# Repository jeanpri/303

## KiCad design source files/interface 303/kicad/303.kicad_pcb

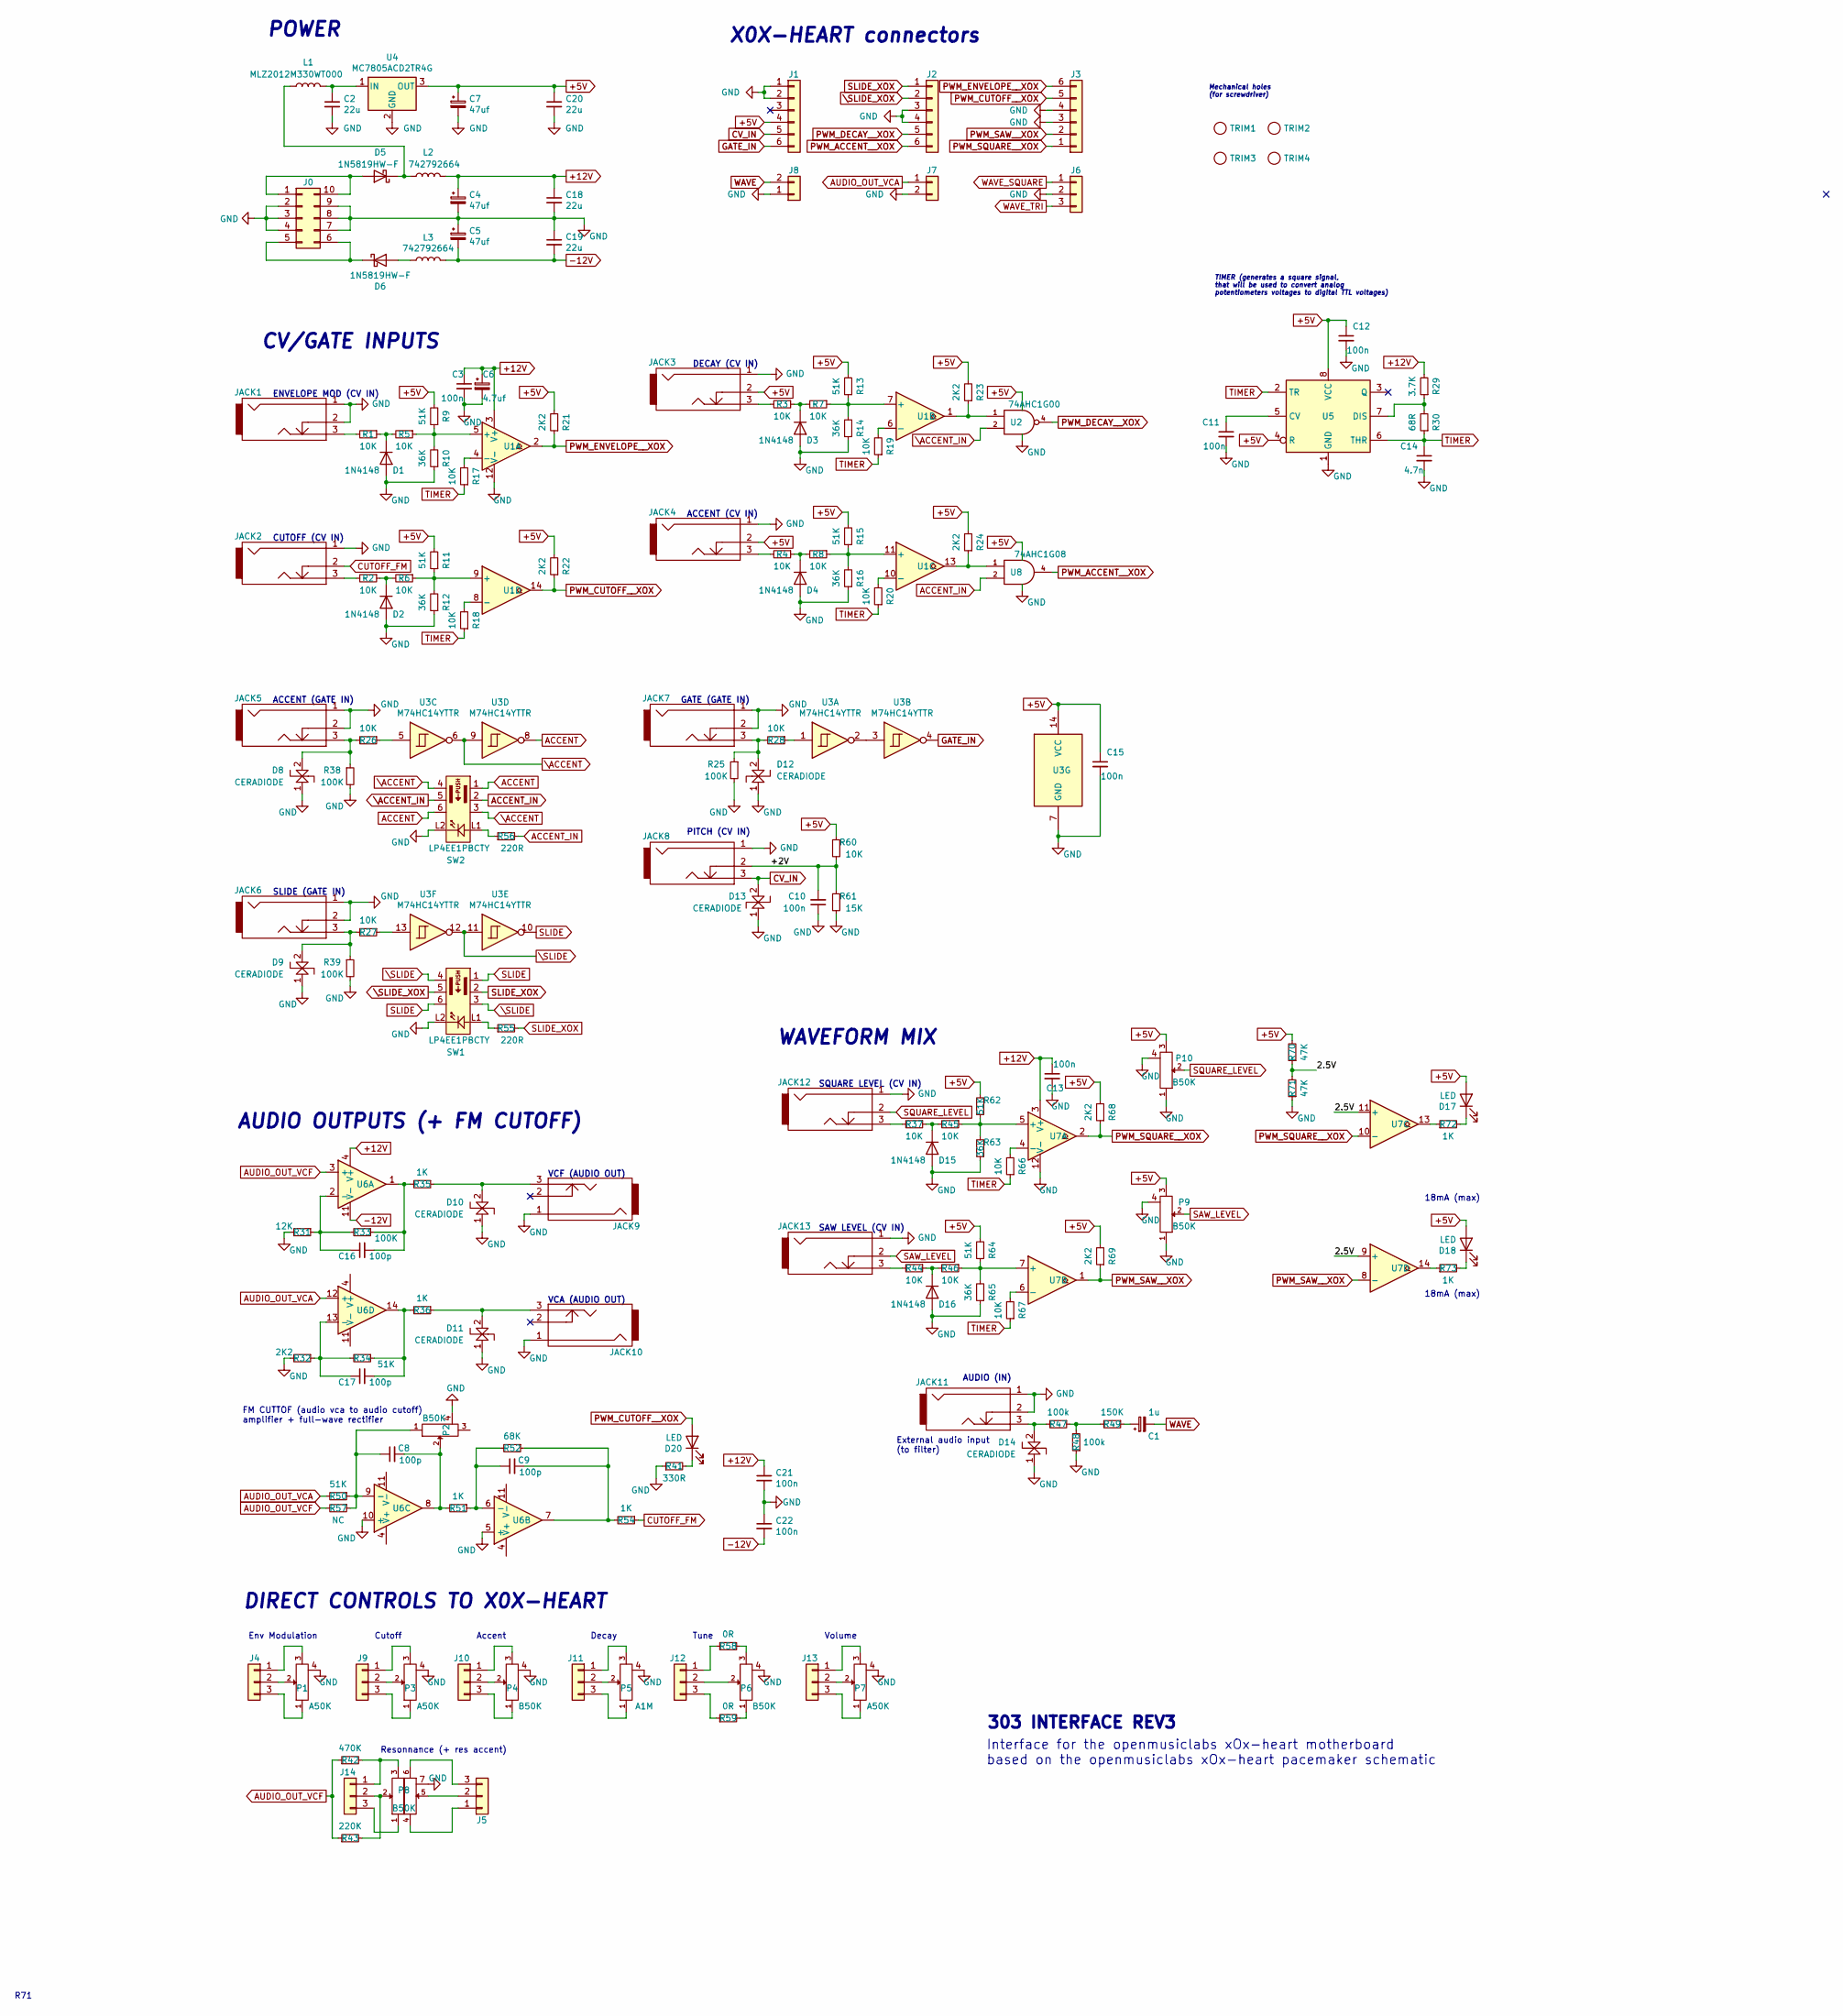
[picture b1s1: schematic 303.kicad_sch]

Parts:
C1: 1u; CP_4x5.3
C2, C18, C19, C20: 22u; C_1206
C3, C10, C11, C12, C13, C15, C21, C22: 100n; C_0603
C4, C5, C7: 47uf; CP_6.3x5.8
C6: 4.7uf; CP_5x5.8
C8, C9, C16, C17: 100p; C_0603
C14: 4.7n; C_0603
D1, D2, D3, D4, D15, D16: 1N4148; D_SOD-123
D5, D6: 1N5819HW-F; D_SOD-123
D8, D9, D10, D11, D12, D13, D14: CERADIODE; CERA_0603
D17, D18, D20: LED; LED_D3.0mm
J0: 30310-6002HB
J1, J2, J3: Conn_01x06; PinHeader_1x06_P2.54mm_Vertical
J4, J5, J6, J9, J10, J11, J12, J13, J14: Conn_01x03; PinHeader_1x03_P2.54mm_Vertical
J7, J8: Conn_01x02; PinHeader_1x02_P2.54mm_Vertical
JACK1, JACK2, JACK3, JACK4, JACK12, JACK13: PJ398SM-BLACK; Thonkiconn_small_head_to_head
JACK5, JACK6, JACK7, JACK8, JACK9, JACK10, JACK11: PJ398SM-BLACK; Thonkiconn_small
L1: MLZ2012M330WT000; R_0805
L2, L3: 742792664; R_0603
P1, P3, P7: A50K; Alpha9mm
P2, P4, P6, P9, P10: B50K; Alpha9mm
P5: A1M; Alpha9mm
P8: B50K; Alpha9mm_dual
R1, R2, R3, R4, R5, R6, R7, R8, R17, R18, R19, R20, R26, R27, R28, R37, R44, R45, R46, R60, R66, R67: 10K; R_0805
R9, R11, R13, R15, R34, R50, R62, R64: 51K; R_0805
R10, R12, R14, R16, R63, R65: 36K; R_0805
R21, R22, R23, R24, R32, R68, R69: 2K2; R_0805
R25, R33, R38, R39: 100K; R_0805
R29: 3.7K; R_0805
R30: 68R; R_0805
R31: 12K; R_0805
R35, R36, R51, R54, R72, R73: 1K; R_0805
R41: 330R; R_0805
R42: 470K; R_0805
R43: 220K; R_0805
R47, R48: 100k; R_0805
R49: 150K; R_0805
R52: 68K; R_0805
R55, R56: 220R; R_0805
R57: NC; R_0805
R58, R59: 0R; R_0805
R61: 15K; R_0805
R70, R71: 47K; R_0805
SW1, SW2: LP4EE1PBCTY; LP4EE1PBCT
TRIM1, TRIM2, TRIM3, TRIM4: TRIM; HOLE_5_2mm
U1, U7: LM339AMX/NOPB; SOIC-14_3.9x8.7mm_P1.27mm
U2: 74AHC1G00; SOT-23-5
U3: M74HC14YTTR; TSSOP-14_4.4x5mm_P0.65mm
U4: MC7805ACD2TR4G; TO-263-3_TabPin2
U5: LM555CMMX/NOPB; VSSOP-8_3.0x3.0mm_P0.65mm
U6: TL074IDE4; SOIC-14_3.9x8.7mm_P1.27mm
U8: 74AHC1G08; SOT-23-5

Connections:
+5V: C7.1, C12.1, C15.1, C20.1, D17.2 (A), D18.2 (A), J1.4, JACK3.2, JACK4.2, P9.3, P10.3, R9.2, R11.2, R13.2, R15.2, R21.2, R22.2, R23.2, R24.2, R60.1, R62.2, R64.2, R68.2, R69.2, R70.2, U2.5 (VCC), U3.14 (VCC), U4.3 (OUT), U5.4 (R), U5.8 (VCC), U8.5 (VCC)
+12V: C3.1, C4.1, C6.1, C13.1, C18.1, C21.1, L2.2, R29.2, U1.3 (V+), U6.4 (V+), U7.3 (V+)
-12V: C5.2, C19.2, C22.2, L3.2, U6.11 (V-)
/2.5V: R70.1, R71.2, U7.9 (+), U7.11 (+)
/+2V: C10.2, JACK8.2, R60.2, R61.1
ACCENT: SW2.1, SW2.6, U3.8
ACCENT_IN: R56.2, SW2.2, U8.2
AUDIO_OUT_VCA: J7.1, R50.2, U6.12 (+)
AUDIO_OUT_VCF: R42.1, R43.1, R57.2, U6.3 (+)
CUTOFF_FM: JACK2.2, R54.1
CV_IN: D13.2, J1.5, JACK8.3
GATE_IN: J1.6, U3.4
GND: C2.2, C3.2, C4.2, C5.1, C6.2, C7.2, C10.1, C11.2, C12.2, C13.2, C14.2, C15.2, C18.2, C19.1, C20.2, C21.2, C22.1, D1.2 (A), D2.2 (A), D3.2 (A), D4.2 (A), D8.1, D9.1, D10.1, D11.1, D12.1, D13.1, D14.1, D15.2 (A), D16.2 (A), J0.2, J0.3, J0.4, J0.7, J0.8, J0.9, J1.1, J1.2, J2.3, J2.4, J3.3, J3.4, J6.2, J7.2, J8.1, JACK1.1, JACK1.2, JACK2.1, JACK3.1, JACK4.1, JACK5.1, JACK5.2, JACK6.1, JACK6.2, JACK7.1, JACK7.2, JACK8.1, JACK9.1, JACK10.1, JACK11.1, JACK11.2, JACK12.1, JACK13.1, P1.4 (shield), P2.4 (shield), P3.4 (shield), P4.4 (shield), P5.4 (shield), P6.4 (shield), P7.4 (shield), P8.7 (shield), P9.1, P9.4 (shield), P10.1, P10.4 (shield), R10.1, R12.1, R14.1, R16.1, R25.2, R31.2, R32.2, R38.2, R39.2, R41.1, R48.1, R61.2, R63.1, R65.1, R71.1, SW1.L2, SW2.L2, U1.12 (V-), U2.3 (GND), U3.7 (GND), U4.2 (GND), U5.1 (GND), U6.5 (+), U6.10 (+), U7.12 (V-), U8.3 (GND)
unnamed: C1.1, R49.1
unnamed: C8.2, P2.2, R51.2, U6.8
unnamed: C9.2, R52.1, R54.2, U6.7
unnamed: C16.2, R33.1, R35.2, U6.1
unnamed: C17.2, R34.1, R36.2, U6.14
unnamed: D1.1 (K), R1.1, R5.2
unnamed: D2.1 (K), R2.1, R6.2
unnamed: D3.1 (K), R3.1, R7.2
unnamed: D4.1 (K), R4.1, R8.2
unnamed: D5.2 (A), J0.1, J0.10
unnamed: D5.1 (K), L1.1, L2.1
unnamed: D6.2 (A), L3.1
unnamed: D6.1 (K), J0.5, J0.6
unnamed: D8.2, JACK5.3, R26.2, R38.1
unnamed: D9.2, JACK6.3, R27.2, R39.1
unnamed: D10.2, JACK9.3, R35.1
unnamed: D11.2, JACK10.3, R36.1
unnamed: D12.2, JACK7.3, R25.1, R28.2
unnamed: D14.2, JACK11.3, R47.2
unnamed: D15.1 (K), R37.1, R45.2
unnamed: D16.1 (K), R44.1, R46.2
unnamed: D17.1 (K), R72.2
unnamed: D18.1 (K), R73.2
unnamed: D20.1 (K), R41.2
unnamed: J4.1, P1.3
unnamed: J4.2, P1.2
unnamed: J4.3, P1.1
unnamed: J5.1, P8.4
unnamed: J5.2, P8.5
unnamed: J5.3, P8.6
unnamed: J9.1, P3.3
unnamed: J9.2, P3.2
unnamed: J9.3, P3.1
unnamed: J10.1, P4.3
unnamed: J10.2, P4.2
unnamed: J10.3, P4.1
unnamed: J11.1, P5.3
unnamed: J11.2, P5.2
unnamed: J11.3, P5.1
unnamed: J12.1, R58.1
unnamed: J12.2, P6.2
unnamed: J12.3, R59.1
unnamed: J13.1, P7.3
unnamed: J13.2, P7.2
unnamed: J13.3, P7.1
unnamed: J14.1, P8.3, R42.2
unnamed: J14.2, P8.2, R43.2
unnamed: J14.3, P8.1
unnamed: JACK1.3, R1.2
unnamed: JACK2.3, R2.2
unnamed: JACK3.3, R3.2
unnamed: JACK4.3, R4.2
unnamed: JACK12.3, R37.2
unnamed: JACK13.3, R44.2
unnamed: P6.1, R59.2
unnamed: P6.3, R58.2
unnamed: R23.1, U1.1, U2.1
unnamed: R24.1, U1.13, U8.1
unnamed: R26.1, U3.5
unnamed: R27.1, U3.13
unnamed: R28.1, U3.1
unnamed: R47.1, R48.2, R49.2
unnamed: R55.1, SW1.L1
unnamed: R56.1, SW2.L1
unnamed: R72.1, U7.13
unnamed: R73.1, U7.14
unnamed: R5.1, R9.1, R10.2, U1.5 (+)
unnamed: R17.2, U1.4 (-)
unnamed: R7.1, R13.1, R14.2, U1.7 (+)
unnamed: R19.2, U1.6 (-)
unnamed: R8.1, R15.1, R16.2, U1.11 (+)
unnamed: R20.2, U1.10 (-)
unnamed: R6.1, R11.1, R12.2, U1.9 (+)
unnamed: R18.2, U1.8 (-)
unnamed: U3.2, U3.3
unnamed: C2.1, L1.2, U4.1 (IN)
unnamed: C11.1, U5.5 (CV)
unnamed: R29.1, R30.2, U5.7 (DIS)
unnamed: C16.1, R31.1, R33.2, U6.2 (-)
unnamed: C9.1, R51.1, R52.2, U6.6 (-)
unnamed: C8.1, P2.1, R50.1, R57.1, U6.9 (-)
unnamed: C17.1, R32.1, R34.2, U6.13 (-)
unnamed: R45.1, R62.1, R63.2, U7.5 (+)
unnamed: R66.2, U7.4 (-)
unnamed: R46.1, R64.1, R65.2, U7.7 (+)
unnamed: R67.2, U7.6 (-)
PWM_ACCENT__XOX: J2.6, U8.4
PWM_CUTOFF__XOX: D20.2 (A), J3.5, R22.1, U1.14
PWM_DECAY__XOX: J2.5, U2.4
PWM_ENVELOPE__XOX: J3.6, R21.1, U1.2
PWM_SAW__XOX: J3.2, R69.1, U7.1, U7.8 (-)
PWM_SQUARE__XOX: J3.1, R68.1, U7.2, U7.10 (-)
SAW_LEVEL: JACK13.2, P9.2
SLIDE: SW1.1, SW1.6, U3.10
SLIDE_XOX: J2.1, R55.2, SW1.2
SQUARE_LEVEL: JACK12.2, P10.2
TIMER: C14.1, R17.1, R18.1, R19.1, R20.1, R30.1, R66.1, R67.1, U5.2 (TR), U5.6 (THR)
WAVE: C1.2, J8.2
WAVE_SQUARE: J6.1
WAVE_TRI: J6.3
\ACCENT: SW2.3, SW2.4, U3.6, U3.9
\ACCENT_IN: SW2.5, U2.2
\SLIDE: SW1.3, SW1.4, U3.11, U3.12
\SLIDE_XOX: J2.2, SW1.5

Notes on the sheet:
303 INTERFACE REV3
Tune
AUDIO (IN)
WAVEFORM MIX
Decay
VCF (AUDIO OUT)
AUDIO OUTPUTS (+ FM CUTOFF)
Cutoff
CV/GATE INPUTS
POWER
TIMER (generates a square signal, that will be used to convert analog potentiometers voltages to digital TTL voltages)
FM CUTTOF (audio vca to audio cutoff) amplifier + full-wave rectifier
VCA (AUDIO OUT)
Resonnance (+ res accent)
SAW LEVEL (CV IN)
R71
ENVELOPE MOD (CV IN)
SQUARE LEVEL (CV IN)
X0X-HEART connectors
SLIDE (GATE IN)
DECAY (CV IN)
Interface for the openmusiclabs xOx-heart motherboard based on the openmusiclabs xOx-heart pacemaker schematic
Mechanical holes (for screwdriver)
Env Modulation
18mA (max)
DIRECT CONTROLS TO X0X-HEART
PITCH (CV IN)
ACCENT (CV IN)
CUTOFF (CV IN)
Volume
ACCENT (GATE IN)
GATE (GATE IN)
Accent
External audio input (to filter)

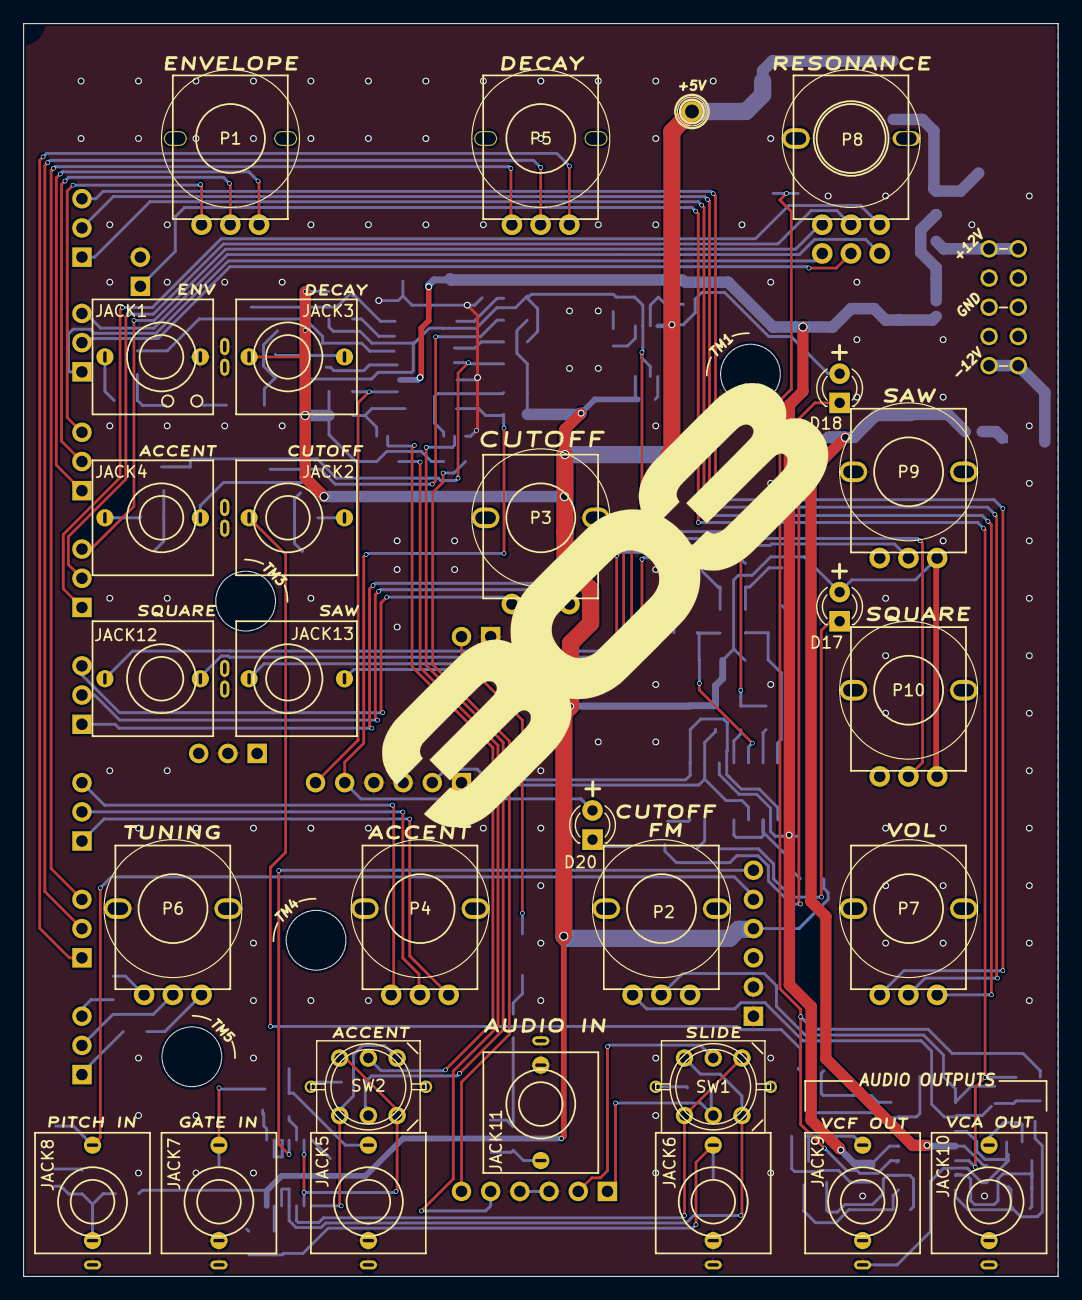
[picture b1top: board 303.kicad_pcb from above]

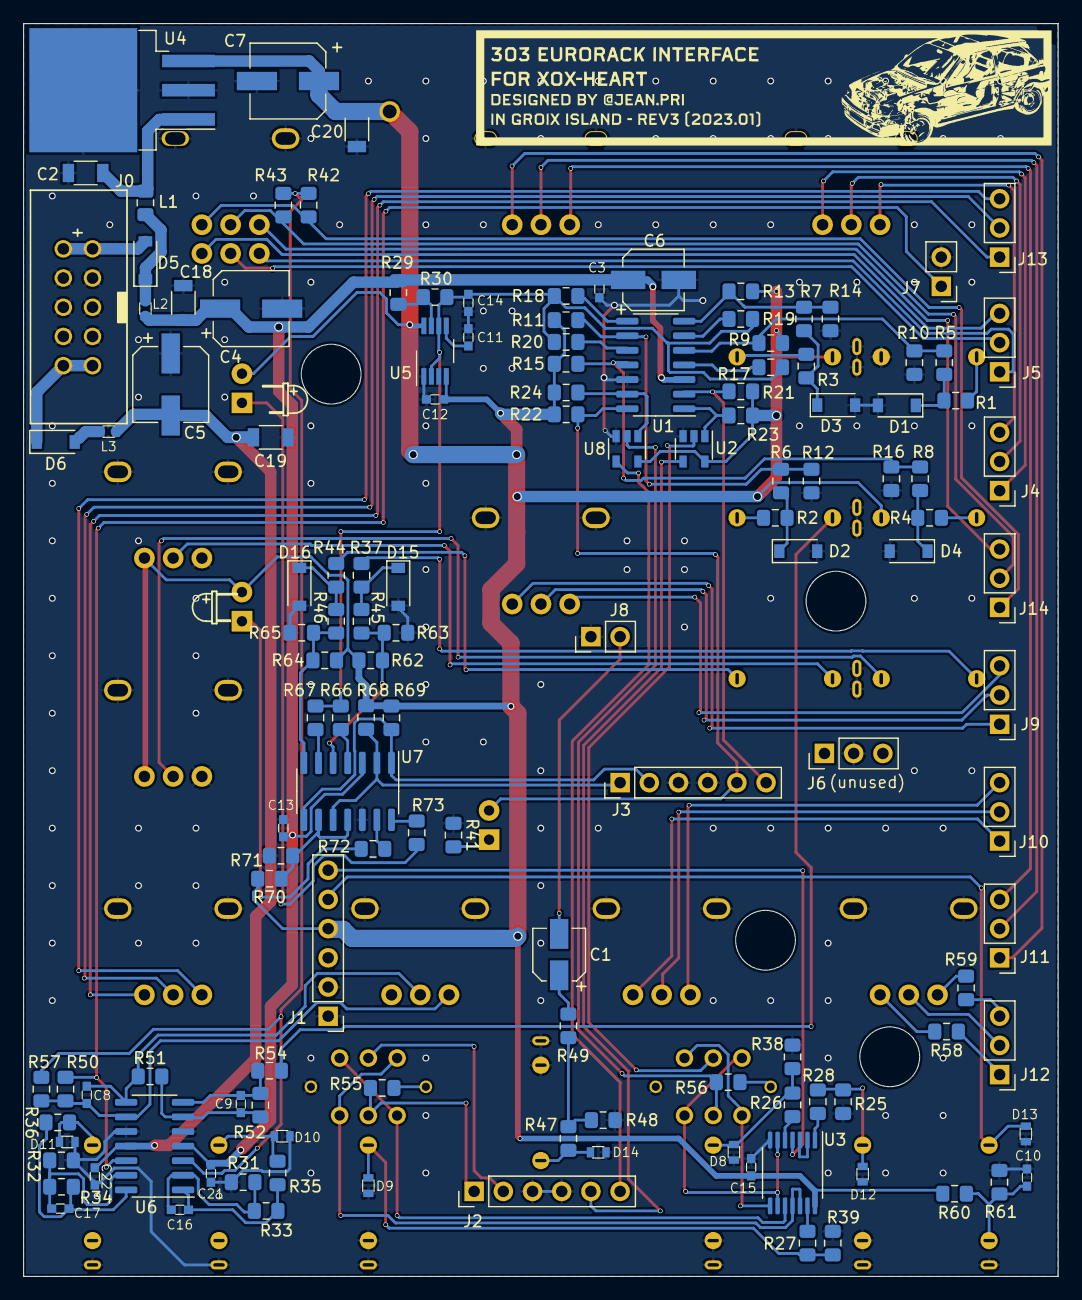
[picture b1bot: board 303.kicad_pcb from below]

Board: 2 copper layers, 90.0 x 109.0 mm, 166 parts (134 on the bottom side), 115 nets.

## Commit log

2026-05-11 Create panel 303 v2
2026-05-18 new faceplate for ei303
